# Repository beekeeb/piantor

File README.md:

# Piantor Keyboard

The Piantor Keyboard is a 42-key or 36-key wired, diodeless, non-flippable, low profile choc v1 (hybrid hotswap and non-hotswap/soldered-in), aggressive column staggered, programmable ergonomic mechnical split keyboard powered by Rasyberry Pi Pico or other compatible RP2040 boards. It is based on the [Cantor Keyboard](https://github.com/diepala/cantor). The name "Piantor" is the portmanteau of "Pico" and "Cantor".

The development of this project is sponsored by [PCBWay](https://pcbway.com/g/beekeeb) (affiliate link).

## Quick Links

* [Build guide](https://docs.beekeeb.com/piantor-keyboard#build-guide)
* [Precompiled firmware](https://docs.beekeeb.com/piantor-keyboard#precompiled-firmware)
* [beekeeb showcase](https://showcase.beekeeb.com/piantor-keyboard/)

## Features

* RP2040 MCU - A low-cost, easy-to-source, powerful microcontroller with dual Arm Cortex-M0+ @ 133MHz, 264kB on-chip SRAM and 2MB (up to 16MB, depending on the breakout board) off-chip external flash memory. You can enable a lot of features and layers. Never worry about the firmware size limit.
* Cantor layout - Ergonomic strong column staggering for short pinkies.
* Non-flippable PCBs - Fewer ways to make mistakes when you install the controller breakout boards. Great for first time keyboard builders.
* Diodeless - A more robust build with fewer things to solder or break.
* Hybrid hotswap and soldered-in low profile choc switches - Experiment with different key switches with the hotswap sockets, or solder the key switches for a more stable build.
* Breakable pinky column - Easily convert the PCB from a 42-key to 36-key layout. You can snap off the pinky column without specialized tools.

## Bill of Materials (BOM)

Quantity | Item | Notes
--- | --- | ---
1 | Piantor PCB (Left)
1 | Piantor PCB (Right)
2 | RP2040 breakout boards (such as Raspberry Pi Pico or WeAct RP2040)
42 (or 36) | Kailh choc v1 PG1350 switches
42 (or 36) | "choc spacing" choc v1 keycaps
2 | TRRS jack (PJ-320A)
1 | 3.5mm TRRS cable | TRS cable cannot be used
42 (or 36) | CPG135001S30 hotswap sockets for choc v1 PG1350 | Optional, you can solder the switches directly if you do not use hotswap sockets
4 | Pin headers (20p) or sockets  | Only required for boards without castellated holes
2 | 10kΩ 1206 (3216M) SMD resistor | Only required if you do not want to use SPLIT_USB DETECT, and for boards without a built in VBUS_SENSE circuit
2 | 5.6kΩ 1206 (3216M) SMD resistor | Only required if you do not want to use SPLIT_USB DETECT, and for boards without a built in VBUS_SENSE circuit

* Note: Raspberry Pi Pico comes with castellated holes and a built in VBUS_SENSE circuit

## Ordering Parts

[DIY kits](https://shop.beekeeb.com/product/piantor-keyboard-kit/) and [prebuilt keyboards](https://shop.beekeeb.com/product/pre-soldered-piantor-split-keyboard/) are available at https://beekeeb.shop

If you prefer getting the parts by yourself, you can order the [Left Side PCB](https://www.pcbway.com/project/shareproject/Piantor_Keyboard_Left_side_24a2937f.html) and the [Right Side PCB](https://www.pcbway.com/project/shareproject/Piantor_Keyboard_Right_side_7c5b31eb.html).

A single side should cost around $31 for 5 pcs excluding shipping. For both sides, it should be around $62 in total for 5 sets.

## Firmware Status

* [QMK](https://github.com/qmk/qmk_firmware) - supported
* [Vial](https://github.com/beekeeb/vial-qmk-piantor) (based on QMK) - supported
* KMK (Python/CircuitPython) - pull request at https://github.com/KMKfw/kmk_firmware/pull/723
* [An example of KMK with miryoku](https://github.com/hansamann/piantor_miryoku_mac) by [hansamann](https://github.com/hansamann) (**this firware requires an older version of kmk from 2022 [repo link](https://github.com/KMKfw/kmk_firmware/tree/b3ec37e2746a854a320e13b1be7823f7902aa658)**)
* Remap - support planned (No ETA)
* PRK (Ruby) - support planned (No ETA)
* keyberon (Rust) - support planned (No ETA)
* ZMK - waiting for [wired split support](https://github.com/zmkfirmware/zmk/issues/1110)

Precompiled firmware can be found at https://docs.beekeeb.com/piantor-keyboard.

## Cases

* [Piantor Gasket Mount Case by chewiedies](https://www.printables.com/model/536044-piantor-gasket-mount-case)
* [Piantor 36-key case with Tenting & Magnets! by Daave](https://www.printables.com/model/381730-piantor-36-key-case-with-tenting-magnets)
* [Travel case for Piantor keyboards by Rilton](https://www.printables.com/model/558902-travel-case-for-piantor-keyboards)

### Piantor Case with a Switch Plate (3D Printable)

The 3D printable case can be founded in the [case folder](./case). The switch plate is optional for the non-hotswap version.

GB823 M2 stainless steel screws with small pan heads are recommended.

* Screw Length
  * No switch plates: 4mm
  * With Switch plates: 6mm
  * With Switch plates and [Donut0804](https://shop.beekeeb.com/product/donut-silicone-rubber-feet-and-pads-o-rings-washers-like/)/o-rings: 7mm

Do not over-tighten the screws.

### Cantor Tray Case

The [Cantor Tray Case](https://www.thingiverse.com/thing:5382705) by chewiedies can be used. There is not a switch plate so it is not recommended for the hotswap version.

## Boards Preview

## License

External symbols and footprints are not covered by the LICENSE in this repo.

* [Keebio-Parts.pretty](https://github.com/keebio/Keebio-Parts.pretty) is licensed under the MIT License.
* [keyswitches.pretty](https://github.com/daprice/keyswitches.pretty) is licensed under the Creative Commons Attribution-ShareAlike 4.0 International License.
* [KiCad-RP-Pico](https://github.com/ncarandini/KiCad-RP-Pico) is licensed under the TPCWare KiCad Library License.
## Sponsors

This open source hardware project is sponsored by

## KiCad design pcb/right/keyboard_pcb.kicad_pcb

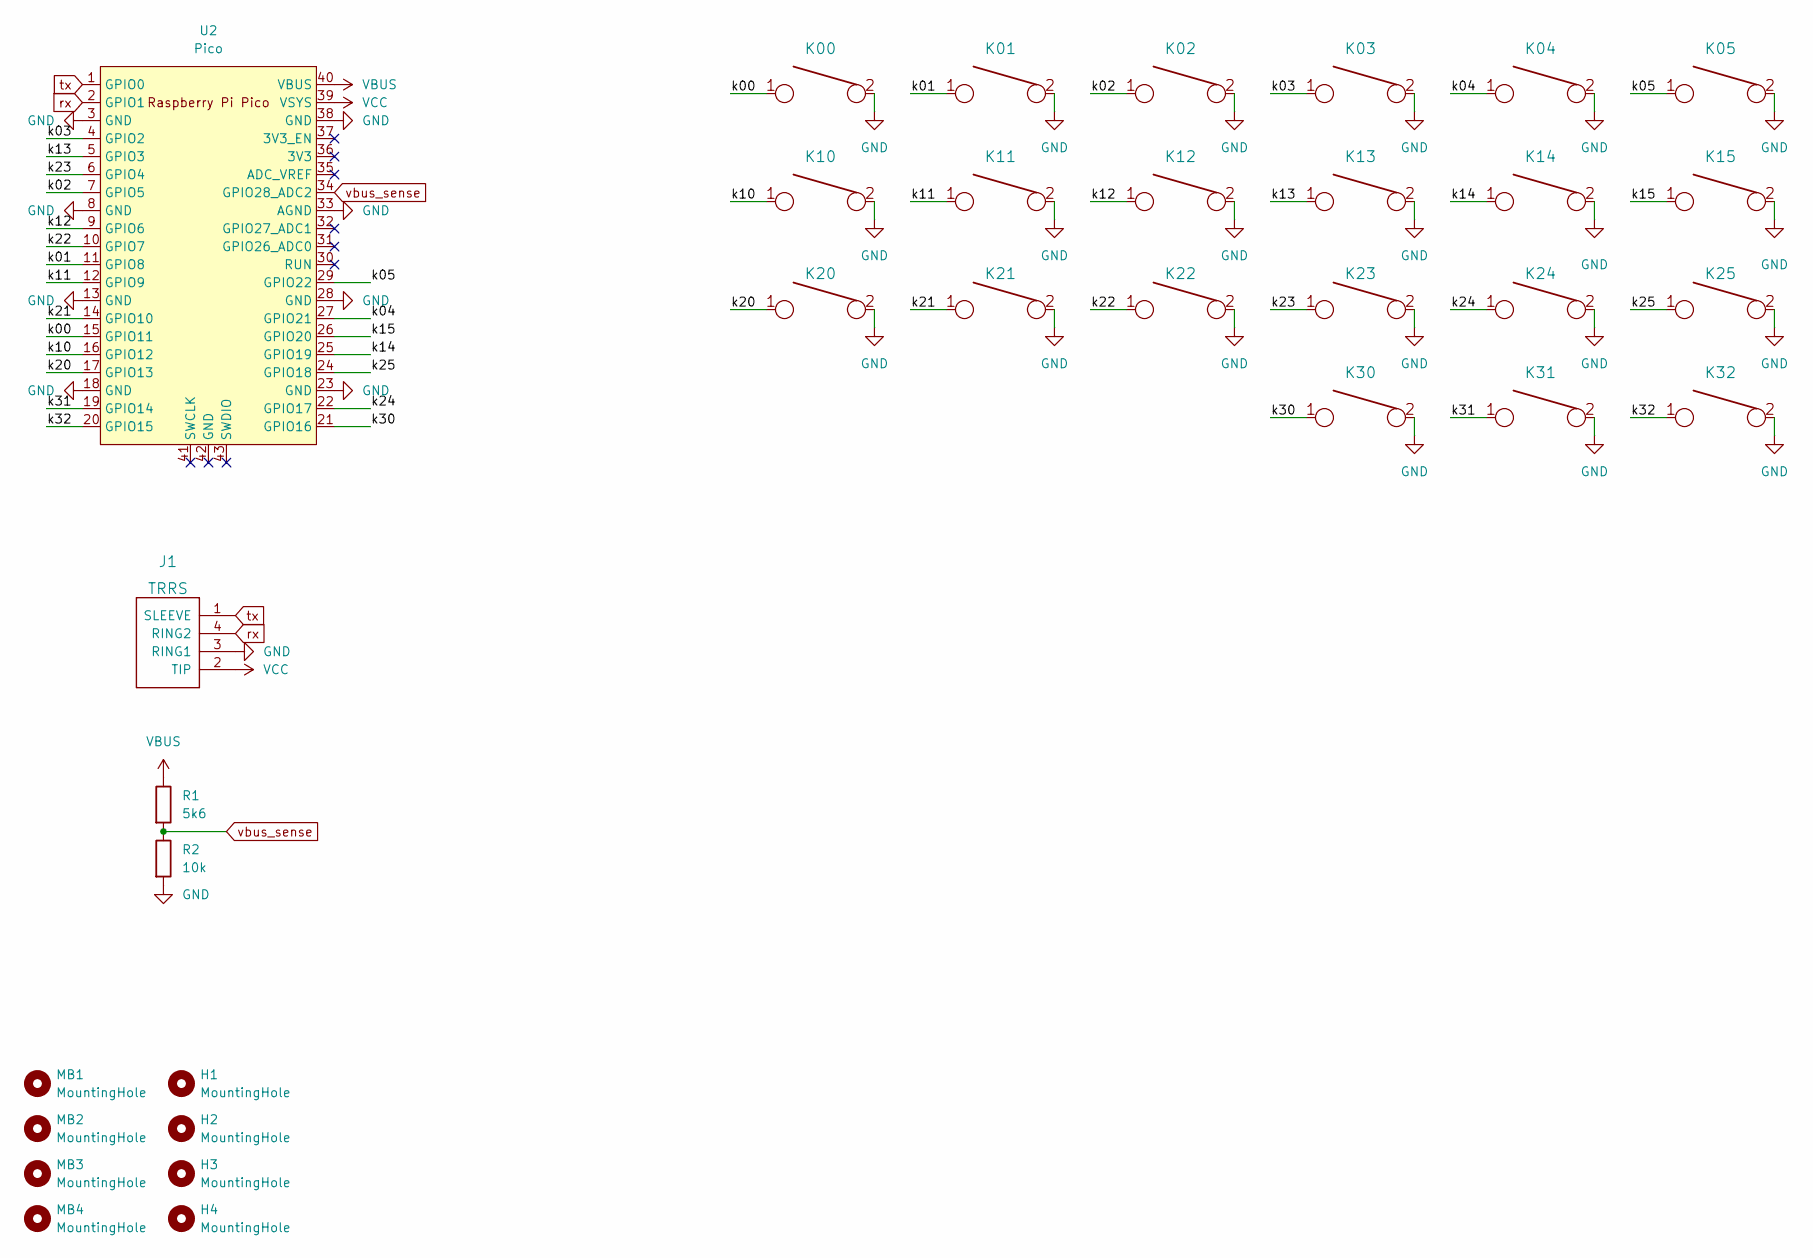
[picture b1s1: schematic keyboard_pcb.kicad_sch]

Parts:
H1, H2, H3, H4: MountingHole; MountingHole_2.2mm_M2-8mm
J1: TRRS; R_1206_3216Metric_Pad1.30x1.75mm_HandSolder
K00, K01, K02, K03, K04, K05, K10, K11, K12, K13, K14, K15, K20, K21, K22, K23, K24, K25, K30, K31, K32: KEYSW; SW_PG1350_reversible
MB1, MB2, MB3, MB4: MountingHole; mousebites
R1: 5k6; R_1206_3216Metric_Pad1.30x1.75mm_HandSolder
R2: 10k; R_1206_3216Metric_Pad1.30x1.75mm_HandSolder
U2: Pico; RPi_Pico_SMD_TH

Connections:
/k00: K00.1, U2.15 (GPIO11)
/k01: K01.1, U2.11 (GPIO8)
/k02: K02.1, U2.7 (GPIO5)
/k03: K03.1, U2.4 (GPIO2)
/k04: K04.1, U2.27 (GPIO21)
/k05: K05.1, U2.29 (GPIO22)
/k10: K10.1, U2.16 (GPIO12)
/k11: K11.1, U2.12 (GPIO9)
/k12: K12.1, U2.9 (GPIO6)
/k13: K13.1, U2.5 (GPIO3)
/k14: K14.1, U2.25 (GPIO19)
/k15: K15.1, U2.26 (GPIO20)
/k20: K20.1, U2.17 (GPIO13)
/k21: K21.1, U2.14 (GPIO10)
/k22: K22.1, U2.10 (GPIO7)
/k23: K23.1, U2.6 (GPIO4)
/k24: K24.1, U2.22 (GPIO17)
/k25: K25.1, U2.24 (GPIO18)
/k30: K30.1, U2.21 (GPIO16)
/k31: K31.1, U2.19 (GPIO14)
/k32: K32.1, U2.20 (GPIO15)
GND: J1.3 (RING1), K00.2, K01.2, K02.2, K03.2, K04.2, K05.2, K10.2, K11.2, K12.2, K13.2, K14.2, K15.2, K20.2, K21.2, K22.2, K23.2, K24.2, K25.2, K30.2, K31.2, K32.2, R2.2, U2.3 (GND), U2.8 (GND), U2.13 (GND), U2.18 (GND), U2.23 (GND), U2.28 (GND), U2.33 (AGND), U2.38 (GND)
VBUS: R1.1, U2.40 (VBUS)
VCC: J1.2 (TIP), U2.39 (VSYS)
rx: J1.4 (RING2), U2.2 (GPIO1)
tx: J1.1 (SLEEVE), U2.1 (GPIO0)
vbus_sense: R1.2, R2.1, U2.34 (GPIO28_ADC2)

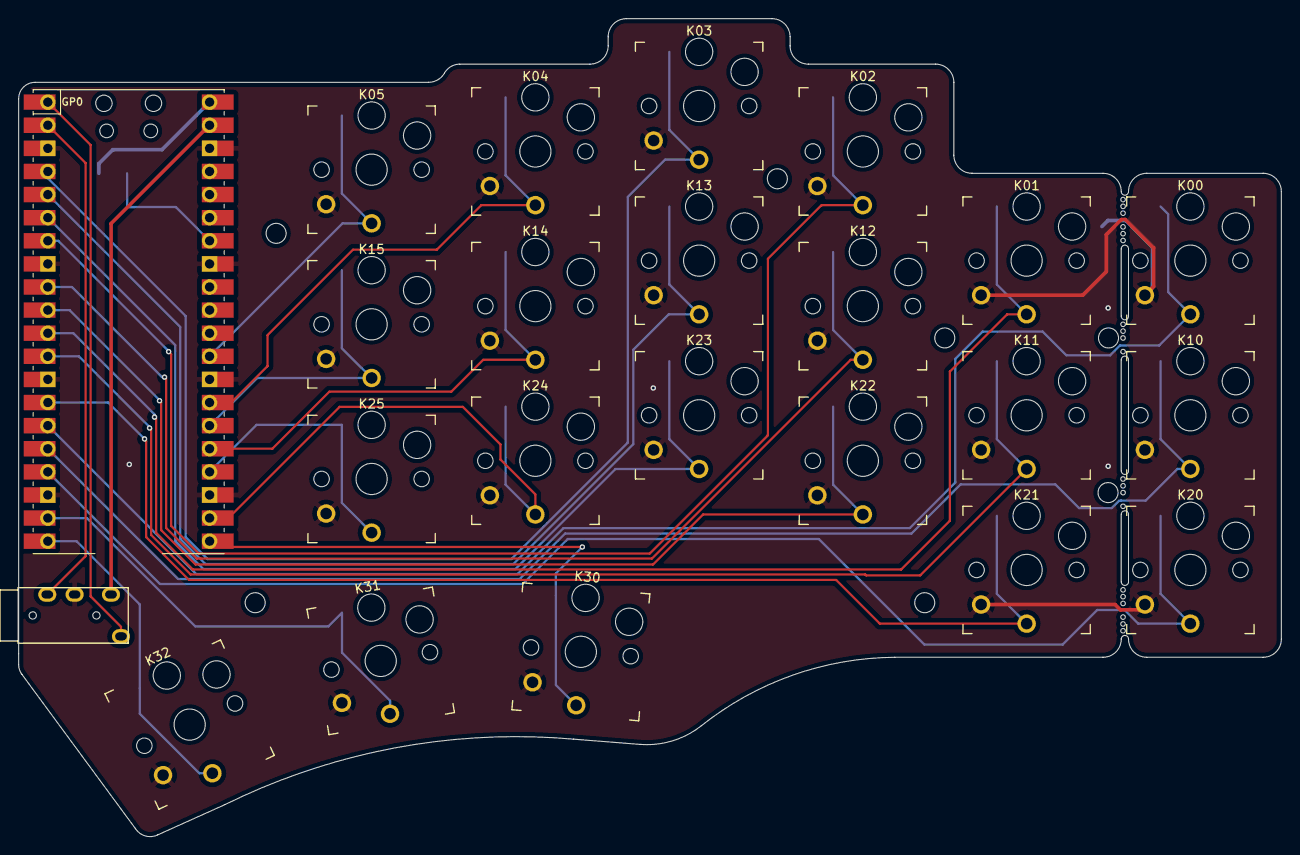
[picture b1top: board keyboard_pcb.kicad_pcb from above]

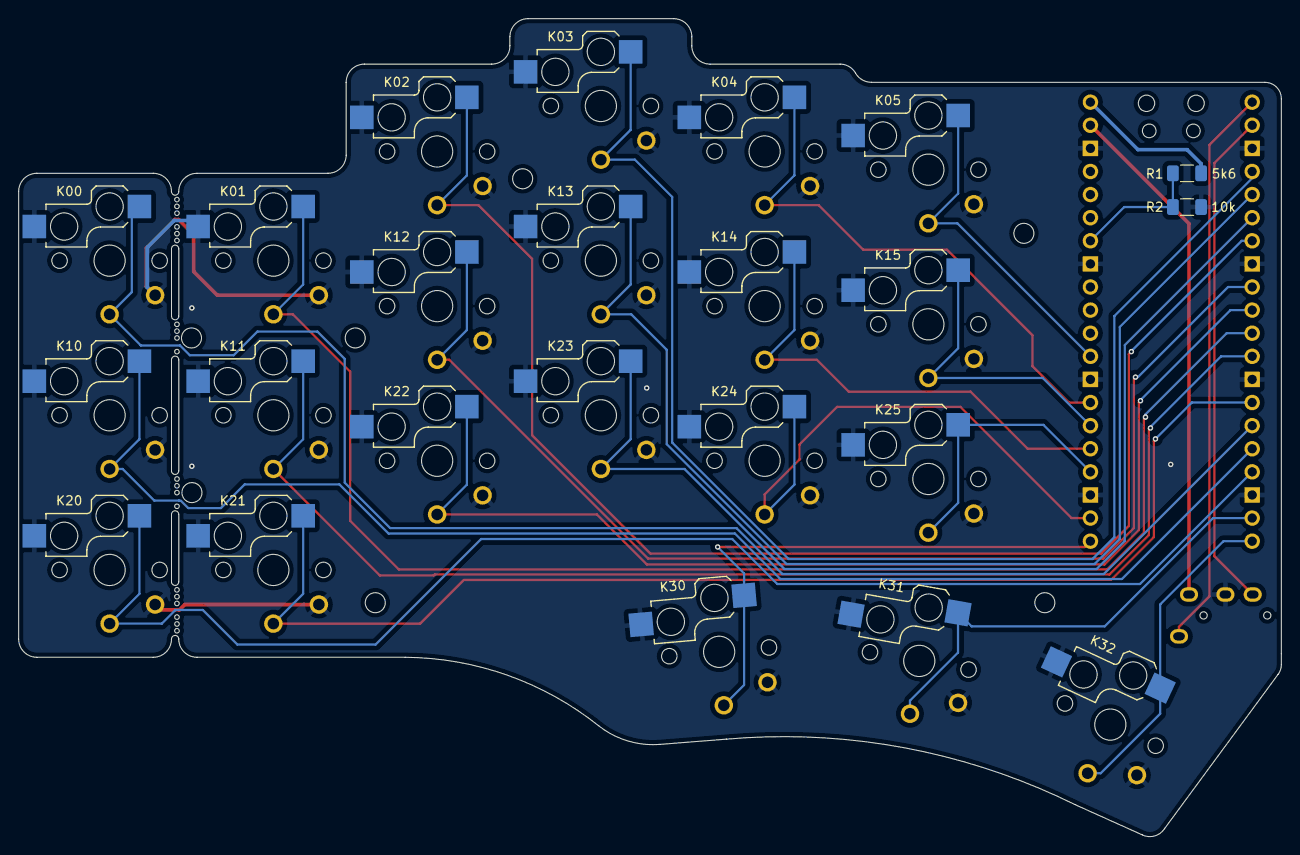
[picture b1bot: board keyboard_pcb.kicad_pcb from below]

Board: 2 copper layers, 138.8 x 89.9 mm, 36 parts (13 on the bottom side), 27 nets.

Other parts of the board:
H1#2, H4#2, H4#3: MountingHole; MountingHole_2.2mm_M2-8mm

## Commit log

2022-11-10 Add case
2023-07-17 36-key .stl files
    Bottom and switch plate files for 36 key Piantor.
2023-10-23 older version of kmk provided in example
    Yhe kmk firmware repository provided in this project requires a version of the kmk firmware from 2022 and this is not specified anywhere in the example repository and it took me a solid hour to figur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

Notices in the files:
README.md:
License: GPL v3
